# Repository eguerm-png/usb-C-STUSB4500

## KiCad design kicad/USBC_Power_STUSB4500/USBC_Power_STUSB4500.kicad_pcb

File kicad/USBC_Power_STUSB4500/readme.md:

## Evaluation Board for the STUSB4500

This is the dual-channel USB-C power supply PCB for the NinjaNIRS system (based on figure 10 of STUSB4500 datasheet which can be found @ usb-C-STUSB4500/datasheets/DS_stusb4500.pdf )

Question: should I use figure 9 instead, since it is fixed PDO and no MCU which is our application of the STUS?

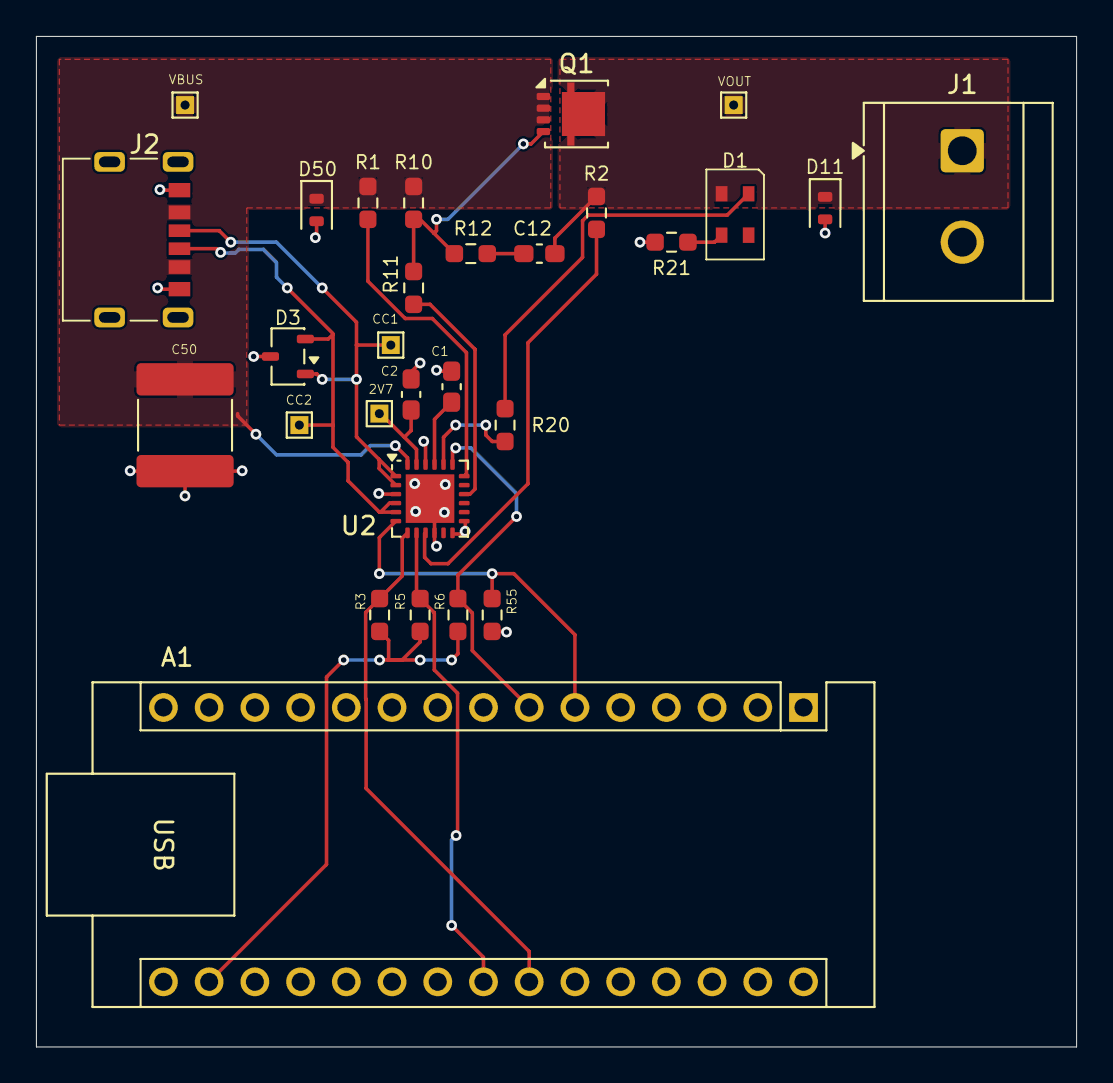
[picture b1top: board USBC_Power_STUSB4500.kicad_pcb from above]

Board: 2 copper layers, 57.8 x 56.1 mm, 29 parts (0 on the bottom side), 20 nets.

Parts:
A1: Arduino_Nano_v3.x; Arduino_Nano
C1, C2: 1uF; C_0603_1608Metric_Pad1.08x0.95mm_HandSolder
C12: 100nF; C_0603_1608Metric_Pad1.08x0.95mm_HandSolder
C50: 4.7uF; C_2220_5750Metric
D1: LTST-C19HE1WT; LED_Avago_PLCC4_3.2x2.8mm_CW
D3: ESDA5V3L; SOT-23-3
D11, D50: ESDA25P35; D_SOD-323
J1: Screw_Terminal_01x02; TerminalBlock_CUI_TB007-508-02_1x02_P5.08mm_Horizontal
J2: USB_C_Receptacle_PowerOnly_6P; Amp_10164359_USB_Power
Q1: STL6P3LLH6; STL6P3LLH6_VSON-8_3.3x3.3mm_P0.65mm_NexFET
R1, R2: 1k; R_0603_1608Metric_Pad0.98x0.95mm_HandSolder
R3, R5, R6: 4.7k; R_0603_1608Metric_Pad0.98x0.95mm_HandSolder
R10: 100k; R_0603_1608Metric_Pad0.98x0.95mm_HandSolder
R11, R20, R21: 22k; R_0603_1608Metric_Pad0.98x0.95mm_HandSolder
R12: 100R; R_0603_1608Metric_Pad0.98x0.95mm_HandSolder
R55: 10k; R_0603_1608Metric_Pad0.98x0.95mm_HandSolder
TP1, TP2, TP5, TP6, TP8: TestPoint_Small; TestPoint_THTPad_1.0x1.0mm_Drill0.5mm
U2: STUSB4500QTR; QFN-24-1EP_4x4mm_P0.5mm_EP2.7x2.7mm

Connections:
/CC1 Test: D3.1 (K), J2.A5 (CC1), TP6.1 (1_1), U2.1 (CC1DB), U2.2 (CC1)
/VBUS: C50.1, D50.1 (K), J2.A9 (VBUS), J2.B9 (VBUS), Q1.1 (S), Q1.2 (S), Q1.3 (S), R1.1, R10.1, TP1.1 (1_1), U2.24 (VDD)
/VOUT: C12.1, D1.4 (A), D11.1 (K), J1.1, Q1.5 (D), R2.1, TP8.1 (1_1)
GND: A1.4 (GND), A1.29 (GND), C1.1, C2.1, C50.2, D3.3 (A), D11.2 (A), D50.2 (A), J1.2, J2.A12 (GND), J2.B12 (GND), J2.S1 (SHIELD), R21.2, R55.2, U2.10 (GND), U2.12 (ADDR0), U2.13 (ADDR1), U2.22 (VSYS), U2.25 (GND)
unnamed: A1.17 (3V3), R3.1, R5.1, R6.1
unnamed: A1.23 (A4), R5.2, U2.8 (SDA)
unnamed: A1.24 (A5), R3.2, U2.7 (SCL)
unnamed: A1.6 (D3), R55.1, U2.6 (RESET)
unnamed: A1.7 (D4), R6.2, U2.19 (ALERT)
unnamed: C12.2, R12.2
unnamed: D1.3 (BK), R21.1
unnamed: D1.1 (RK), R20.1
unnamed: D3.2 (K), J2.B5 (CC2), TP5.1 (1_1), U2.4 (CC2), U2.5 (CC2DB)
unnamed: Q1.4 (G), R10.2, R11.1, R12.1
unnamed: R2.2, U2.9 (DISCH)
unnamed: R20.2, U2.20 (POWER_OK2)
unnamed: R11.2, U2.16 (VBUS_EN_SNK)
unnamed: R1.2, U2.18 (VBUS_VS_DISCH)
unnamed: C1.2, U2.21 (VREG_1V2)
unnamed: C2.2, TP2.1 (1_1), U2.23 (VREG_2V7)
